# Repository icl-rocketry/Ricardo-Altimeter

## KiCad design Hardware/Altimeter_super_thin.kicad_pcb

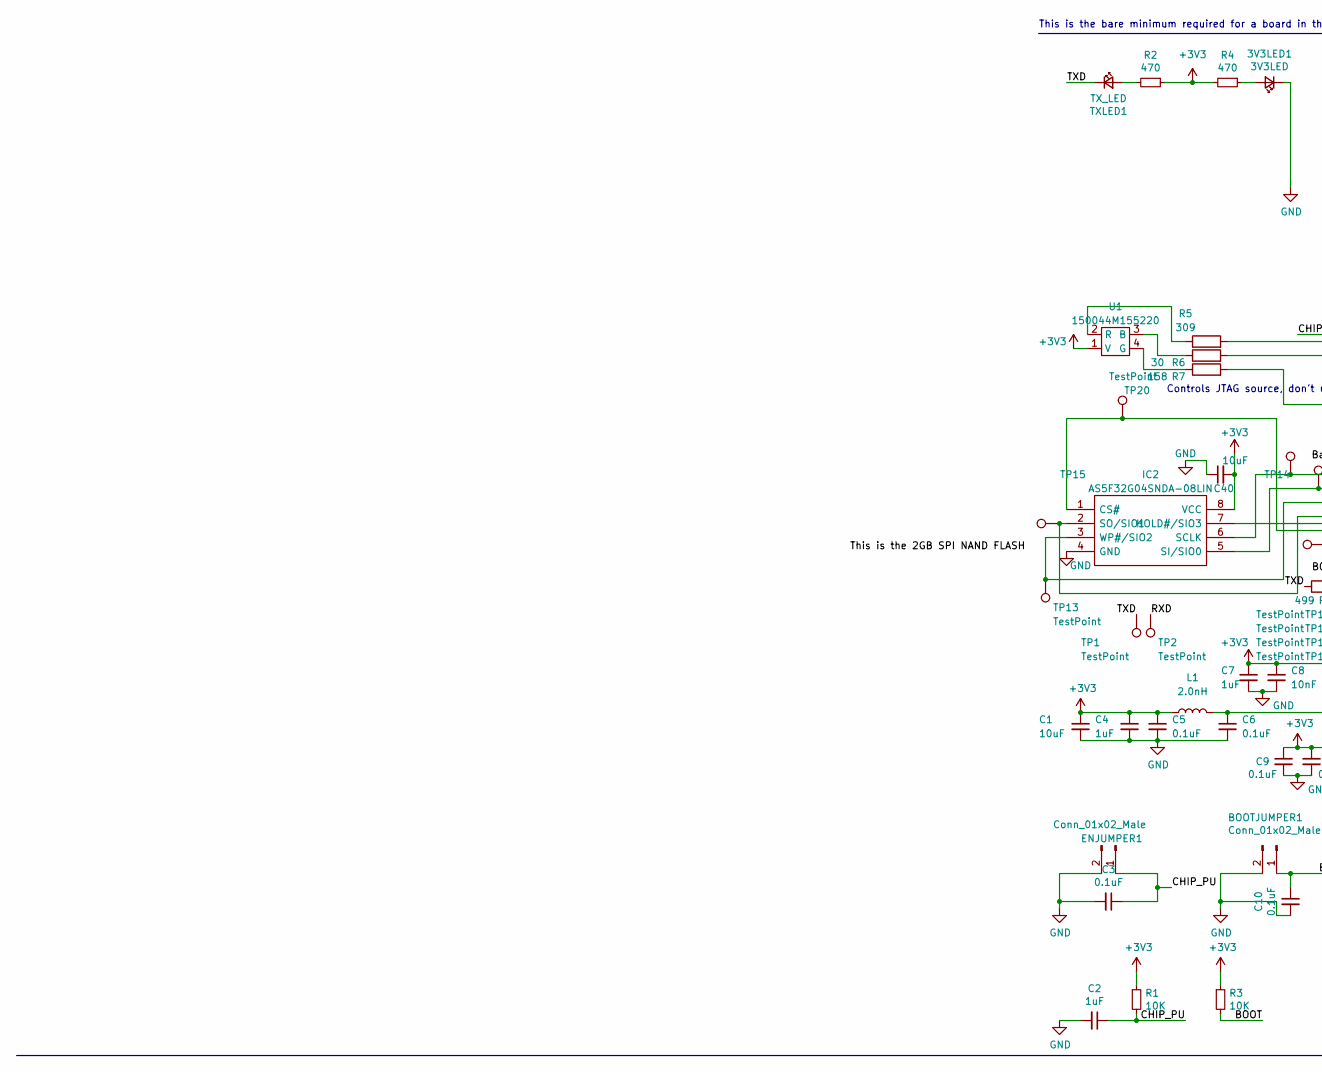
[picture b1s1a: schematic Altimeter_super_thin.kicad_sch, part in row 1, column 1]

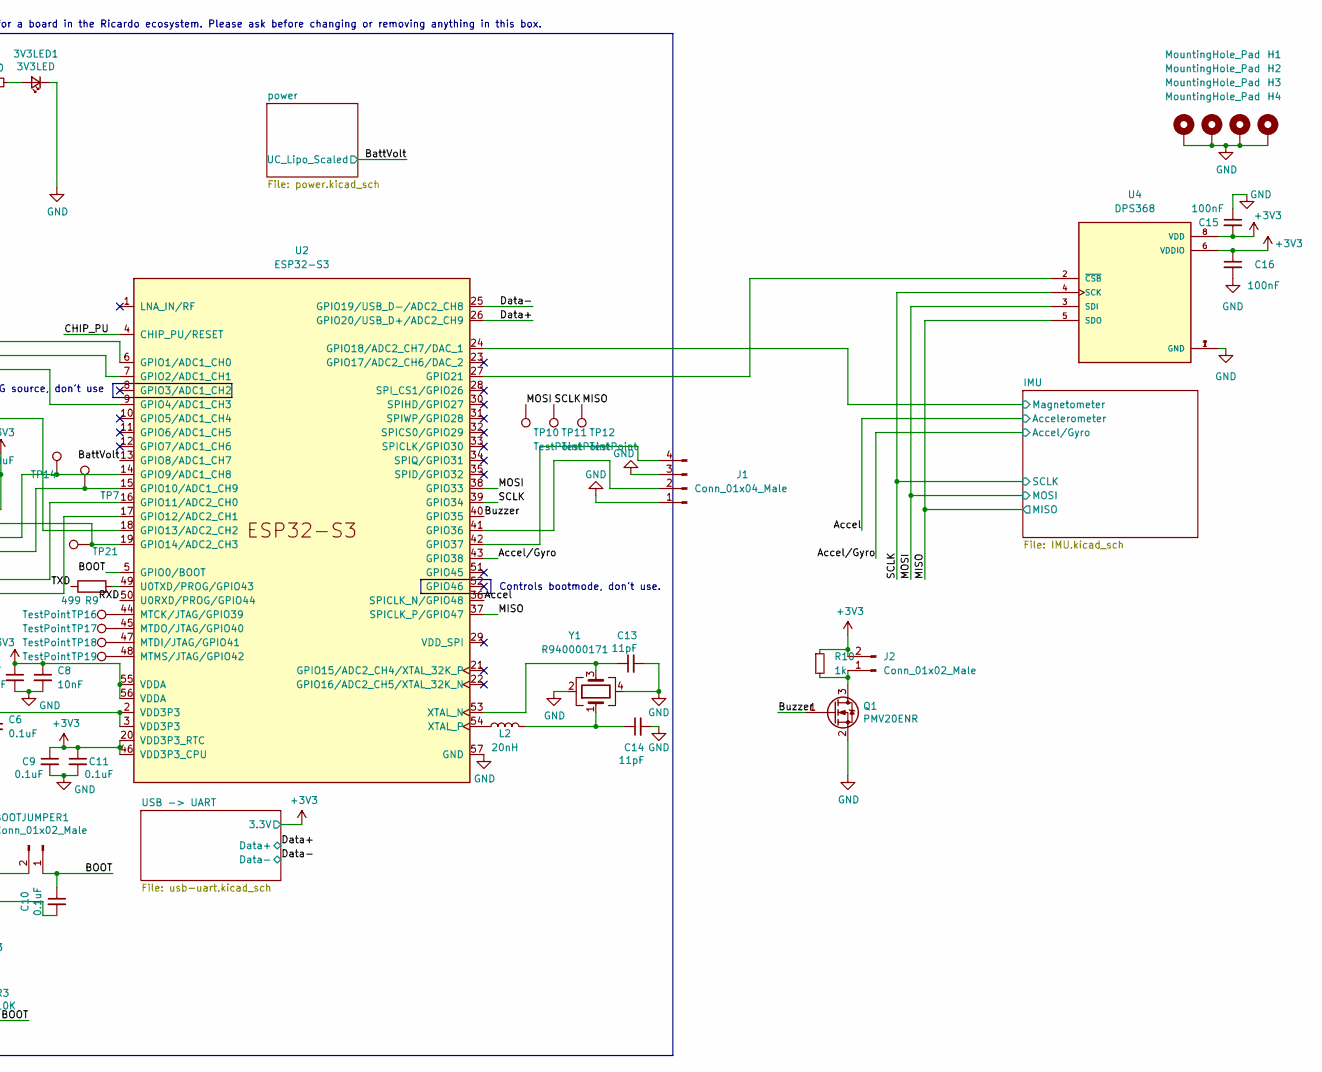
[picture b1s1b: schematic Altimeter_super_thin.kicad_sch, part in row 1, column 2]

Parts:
3V3LED1: 3V3LED; R_0402_1005Metric
BOOTJUMPER1: Conn_01x02_Male; PinHeader_1x02_P2.54mm_Vertical
C1, C40: 10uF; C_0402_1005Metric
C2, C4, C7: 1uF; C_0402_1005Metric
C3, C5, C6, C9, C10, C11: 0.1uF; C_0402_1005Metric
C8: 10nF; C_0402_1005Metric
C13, C14: 11pF; C_0402_1005Metric
C15, C16: 100nF; C_0402_1005Metric
ENJUMPER1: Conn_01x02_Male; PinHeader_1x02_P2.54mm_Vertical
H1, H2, H3, H4: MountingHole_Pad; MountingHole_3.2mm_M3_DIN965
IC2: AS5F32G04SNDA-08LIN; SON127P600X800X65-8N; Manufacturer_Part_Number XTSD08GLGEAG
J1: Conn_01x04_Male; PinHeader_1x04_P2.54mm_Vertical
J2: Conn_01x02_Male; JST_PH_B2B-PH-K_1x02_P2.00mm_Vertical
L1: 2.0nH; L_0402_1005Metric
L2: 20nH; L_0402_1005Metric
Q1: PMV20ENR; SOT-23
R1, R3: 10K; R_0402_1005Metric
R2, R4: 470; R_0402_1005Metric
R5: 309; R_0402_1005Metric
R6: 30; R_0402_1005Metric
R7: 158; R_0402_1005Metric
R9: 499; R_0402_1005Metric
R10: 1k; R_0402_1005Metric
TP1, TP2, TP7, TP10, TP11, TP12, TP13, TP14, TP15, TP16, TP17, TP18, TP19, TP20, TP21: TestPoint; TestPoint_Pad_D1.0mm
TXLED1: TX_LED; R_0402_1005Metric
U1: 150044M155220
U2: ESP32-S3; QFN40P700X700X90-57N
U4: DPS368; XDCR_DPS310
Y1: R940000171; Crystal_SMD_2016-4Pin_2.0x1.6mm

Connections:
+3V3: C1.1, C4.1, C5.1, C7.1, C8.1, C9.1, C11.1, C15.2, C16.1, C40.2, IC2.8 (VCC), J2.2, L1.1, R1.1, R2.1, R3.1, R4.2, R10.1, U1.1 (V), U2.20 (VDD3P3_RTC), U2.46 (VDD3P3_CPU), U2.55 (VDDA), U2.56 (VDDA), U4.6 (VDDIO), U4.8 (VDD); also elsewhere on the board
/Accel: U2.36 (SPICLK_N/GPIO48); also elsewhere on the board
/Accel/Gyro: U2.43 (GPIO38); also elsewhere on the board
/BOOT: BOOTJUMPER1.1, C10.1, R3.2, U2.5 (GPIO0/BOOT)
/BattVolt: U2.13 (GPIO8/ADC1_CH7); also elsewhere on the board
/Buzzer: Q1.1 (G), U2.40 (GPIO35)
/CHIP_PU: C2.1, C3.1, ENJUMPER1.1, R1.2, U2.4 (CHIP_PU/RESET)
/Data+: U2.26 (GPIO20/USB_D+/ADC2_CH9); also elsewhere on the board
/Data-: U2.25 (GPIO19/USB_D-/ADC2_CH8); also elsewhere on the board
/IMU/Magnetometer: U2.24 (GPIO18/ADC2_CH7/DAC_1); also elsewhere on the board
/MISO: TP12.1, U2.37 (SPICLK_P/GPIO47), U4.5 (SDO); also elsewhere on the board
/MOSI: TP10.1, U2.38 (GPIO33), U4.3 (SDI); also elsewhere on the board
/RXD: TP2.1, U2.50 (U0RXD/PROG/GPIO44)
/SCLK: TP11.1, U2.39 (GPIO34), U4.4 (SCK); also elsewhere on the board
/TXD: R9.1, TP1.1, TXLED1.1 (K)
GND: 3V3LED1.1 (K), BOOTJUMPER1.2, C1.2, C2.2, C3.2, C4.2, C5.2, C6.2, C7.2, C8.2, C9.2, C10.2, C11.2, C13.2, C14.2, C15.1, C16.2, C40.1, ENJUMPER1.2, H1.1, H2.1, H3.1, H4.1, IC2.4 (GND), J1.1, J1.3, Q1.2 (S), U2.57 (GND), U4.1 (GND), U4.7 (GND), Y1.2, Y1.4; also elsewhere on the board
unnamed: 3V3LED1.2 (A), R4.1
unnamed: C6.1, L1.2, U2.2 (VDD3P3), U2.3 (VDD3P3)
unnamed: C14.1, L2.2, Y1.1
unnamed: IC2.1 (CS#), TP20.1, U2.18 (GPIO13/ADC2_CH2)
unnamed: IC2.7 (HOLD#/SIO3), TP21.1, U2.19 (GPIO14/ADC2_CH3)
unnamed: IC2.6 (SCLK), TP14.1, U2.14 (GPIO9/ADC1_CH8)
unnamed: IC2.5 (SI/SIO0), TP7.1, U2.15 (GPIO10/ADC1_CH9)
unnamed: IC2.2 (SO/SIO1), TP15.1, U2.17 (GPIO12/ADC2_CH1)
unnamed: IC2.3 (WP#/SIO2), TP13.1, U2.16 (GPIO11/ADC2_CH0)
unnamed: J1.2, U2.41 (GPIO36)
unnamed: J1.4, U2.42 (GPIO37)
unnamed: J2.1, Q1.3 (D), R10.2
unnamed: R2.2, TXLED1.2 (A)
unnamed: R6.1, U1.3 (B)
unnamed: R7.1, U1.4 (G)
unnamed: R5.1, U1.2 (R)
unnamed: R5.2, U2.6 (GPIO1/ADC1_CH0)
unnamed: R6.2, U2.7 (GPIO2/ADC1_CH1)
unnamed: R7.2, U2.9 (GPIO4/ADC1_CH3)
unnamed: U2.27 (GPIO21), U4.2 (~CSB)
unnamed: TP16.1, U2.44 (MTCK/JTAG/GPIO39)
unnamed: TP18.1, U2.47 (MTDI/JTAG/GPIO41)
unnamed: TP17.1, U2.45 (MTDO/JTAG/GPIO40)
unnamed: TP19.1, U2.48 (MTMS/JTAG/GPIO42)
unnamed: R9.2, U2.49 (U0TXD/PROG/GPIO43)
unnamed: C13.1, U2.53 (XTAL_N), Y1.3
unnamed: L2.1, U2.54 (XTAL_P)

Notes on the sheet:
Controls bootmode, don't use.
This is the bare minimum required for a board in the Ricardo ecosystem. Please ask before changing or removing anything in this box.
Controls JTAG source, don't use

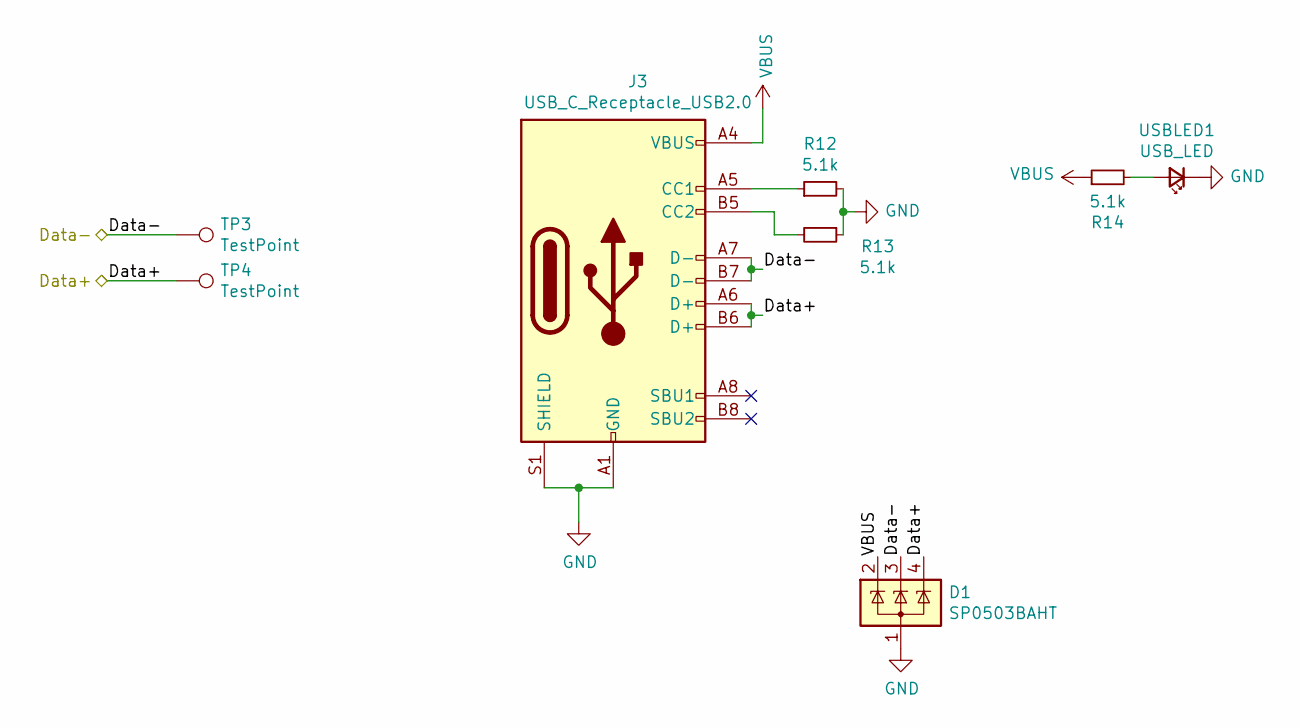
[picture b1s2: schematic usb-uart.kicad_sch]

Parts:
D1: SP0503BAHT; SOT-143
J3: USB_C_Receptacle_USB2.0; USB_C_Receptacle_Palconn_UTC16-G
R12, R13, R14: 5.1k; R_0402_1005Metric
TP3, TP4: TestPoint; TestPoint_Pad_D1.0mm
USBLED1: USB_LED; LED_0402_1005Metric

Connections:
/Data+: D1.4 (K), J3.A6 (D+), J3.B6 (D+), TP4.1; also elsewhere on the board
/Data-: D1.3 (K), J3.A7 (D-), J3.B7 (D-), TP3.1; also elsewhere on the board
GND: D1.1 (A), J3.A1 (GND), J3.A12 (GND), J3.B1 (GND), J3.B12 (GND), J3.S1 (SHIELD), R12.2, R13.1, USBLED1.1 (K); also elsewhere on the board
unnamed: J3.A5 (CC1), R12.1
unnamed: J3.B5 (CC2), R13.2
unnamed: R14.2, USBLED1.2 (A)
VBUS: D1.2 (K), J3.A4 (VBUS), J3.A9 (VBUS), J3.B4 (VBUS), J3.B9 (VBUS), R14.1; also elsewhere on the board

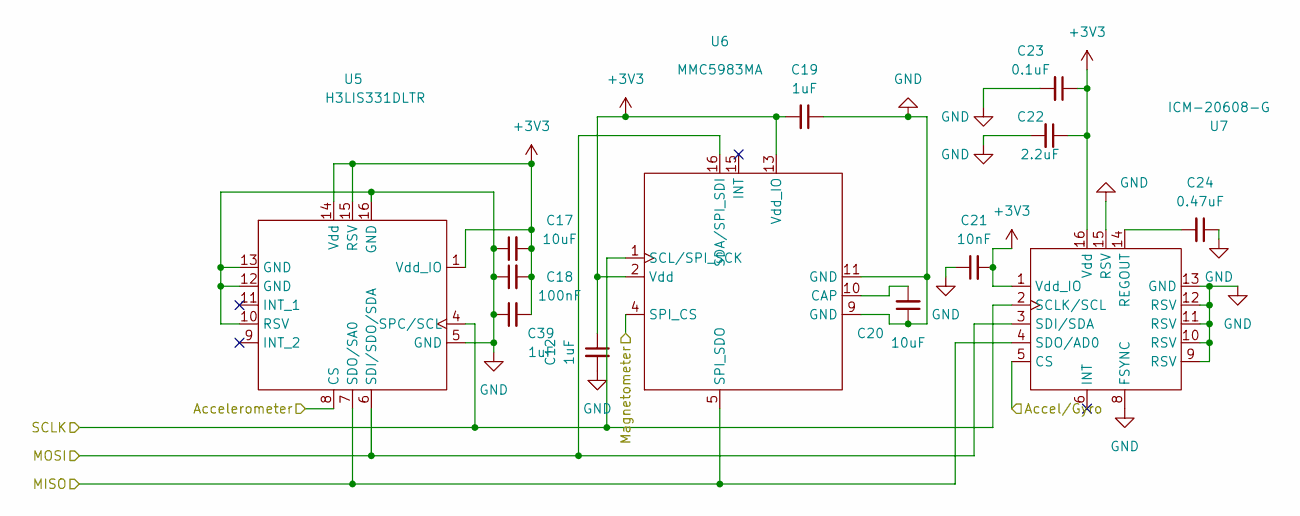
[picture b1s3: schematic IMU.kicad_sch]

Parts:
C12, C19, C39: 1uF; C_0402_1005Metric
C17, C20: 10uF; C_0402_1005Metric
C18: 100nF; C_0402_1005Metric
C21: 10nF; C_0402_1005Metric
C22: 2.2uF; C_0402_1005Metric
C23: 0.1uF; C_0402_1005Metric
C24: 0.47uF; C_0402_1005Metric
U5: H3LIS331DLTR; QFN300X300X100-16N
U6: MMC5983MA; PQFN50P300X300X100-16N
U7: ICM-20608-G; PQFN50P300X300X80-16N

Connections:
+3V3: C12.1, C17.2, C18.2, C19.2, C21.2, C22.1, C23.1, C39.2, U5.1 (Vdd_IO), U5.14 (Vdd), U5.15 (RSV), U6.2 (Vdd), U6.13 (Vdd_IO), U7.1 (Vdd_IO), U7.16 (Vdd); also elsewhere on the board
/Accel: U5.8 (CS); also elsewhere on the board
/Accel/Gyro: U7.5 (CS); also elsewhere on the board
/IMU/Magnetometer: U6.4 (SPI_CS); also elsewhere on the board
/MISO: U5.7 (SDO/SA0), U6.5 (SPI_SDO), U7.4 (SDO/AD0); also elsewhere on the board
/MOSI: U5.6 (SDI/SDO/SDA), U6.16 (SDA/SPI_SDI), U7.3 (SDI/SDA); also elsewhere on the board
/SCLK: U5.4 (SPC/SCL), U6.1 (SCL/SPI_SCK), U7.2 (SCLK/SCL); also elsewhere on the board
GND: C12.2, C17.1, C18.1, C19.1, C20.1, C21.1, C22.2, C23.2, C24.1, C39.1, U5.5 (GND), U5.10 (RSV), U5.12 (GND), U5.13 (GND), U5.16 (GND), U6.9 (GND), U6.11 (GND), U7.8 (FSYNC), U7.9 (RSV), U7.10 (RSV), U7.11 (RSV), U7.12 (RSV), U7.13 (GND), U7.15 (RSV); also elsewhere on the board
unnamed: C20.2, U6.10 (CAP)
unnamed: C24.2, U7.14 (REGOUT)

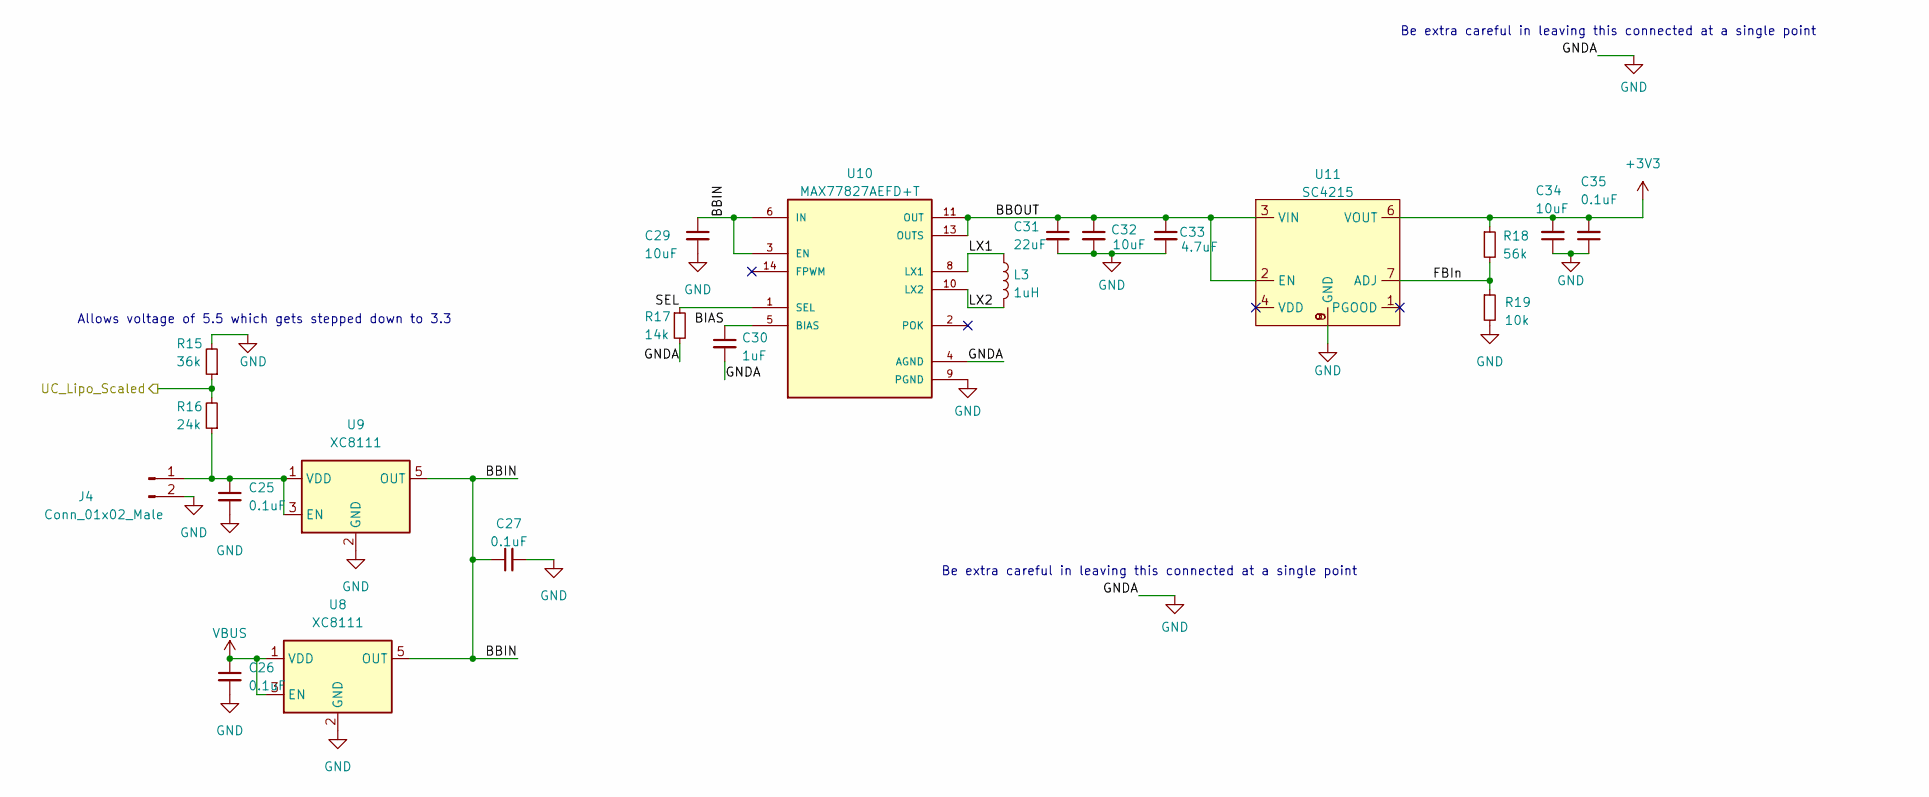
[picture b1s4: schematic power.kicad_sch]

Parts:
C25, C26, C27, C35: 0.1uF; C_0402_1005Metric
C29: 10uF; C_0603_1608Metric
C30: 1uF; C_0402_1005Metric
C31: 22uF; C_0603_1608Metric
C32, C34: 10uF; C_0402_1005Metric
C33: 4.7uF; C_0402_1005Metric
J4: Conn_01x02_Male; JST_PH_B2B-PH-K_1x02_P2.00mm_Vertical
L3: 1uH; L_0805_2012Metric
R15: 36k; R_0402_1005Metric
R16: 24k; R_0402_1005Metric
R17: 14k; R_0402_1005Metric
R18: 56k; R_0402_1005Metric
R19: 10k; R_0402_1005Metric
U8, U9: XC8111; SOT-23-5
U10: MAX77827AEFD+T; CONV_MAX77827AEFD+T; PARTREV B
U11: SC4215; SOIC127P599X175-9N

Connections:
+3V3: C34.2, C35.2, R18.1, U11.6 (VOUT); also elsewhere on the board
/BattVolt: R15.1, R16.2; also elsewhere on the board
/power/BBIN: C27.1, C29.1, U8.5 (OUT), U9.5 (OUT), U10.3 (EN), U10.6 (IN)
/power/BBOUT: C31.1, C32.1, C33.1, U10.11 (OUT), U10.13 (OUTS), U11.2 (EN), U11.3 (VIN)
/power/BIAS: C30.1, U10.5 (BIAS)
/power/FBIn: R18.2, R19.1, U11.7 (ADJ)
/power/LX1: L3.1, U10.8 (LX1)
/power/LX2: L3.2, U10.10 (LX2)
/power/SEL: R17.1, U10.1 (SEL)
GND: C25.2, C26.2, C27.2, C29.2, C30.2, C31.2, C32.2, C33.2, C34.1, C35.1, J4.2, R15.2, R17.2, R19.2, U8.2 (GND), U9.2 (GND), U10.4 (AGND), U10.9 (PGND), U11.8 (GND), U11.9 (GND); also elsewhere on the board
unnamed: C25.1, J4.1, R16.1, U9.1 (VDD), U9.3 (EN)
VBUS: C26.1, U8.1 (VDD), U8.3 (EN); also elsewhere on the board

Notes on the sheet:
Be extra careful in leaving this connected at a single point
Allows voltage of 5.5 which gets stepped down to 3.3

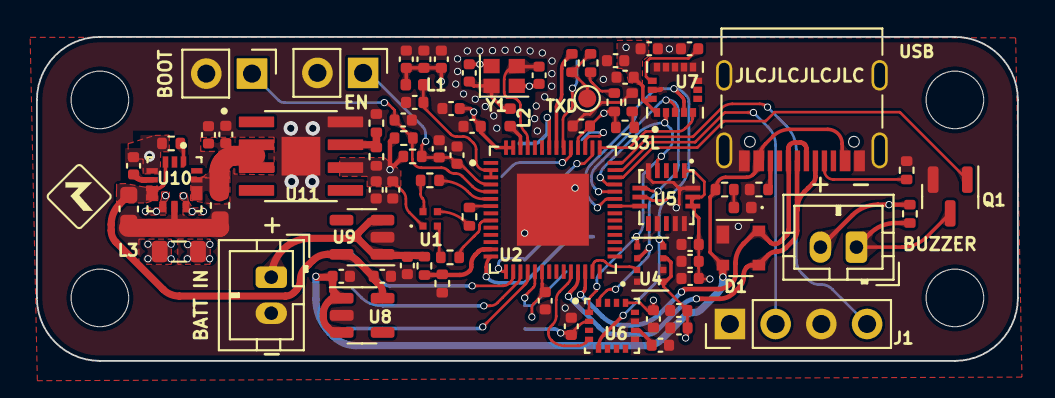
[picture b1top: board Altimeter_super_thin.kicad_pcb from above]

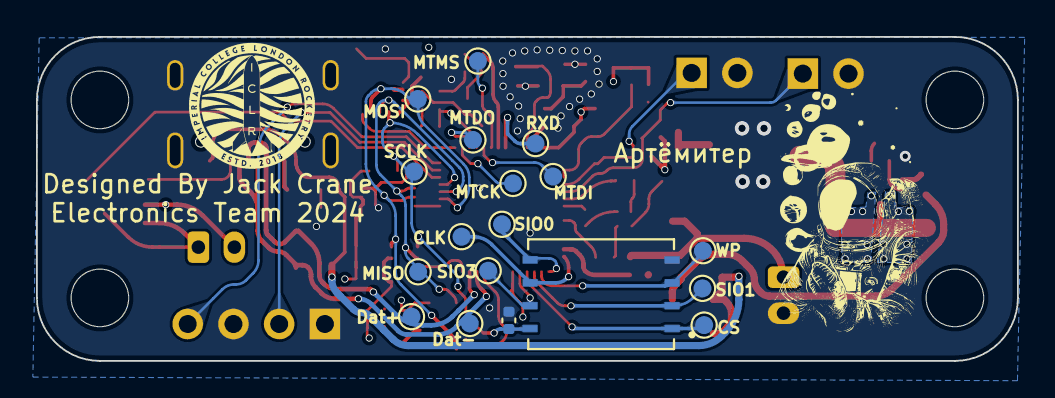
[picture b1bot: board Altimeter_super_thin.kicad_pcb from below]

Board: 4 copper layers, 54.5 x 18.0 mm, 100 parts (18 on the bottom side), 57 nets.

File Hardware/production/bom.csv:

Designator,Footprint,Quantity,Value,LCSC Part #
3V3LED1,0402,1,3V3LED,
"BOOTJUMPER1, ENJUMPER1",PinHeader_1x02_P2.54mm_Vertical,2,Conn_01x02_Male,
"C1, C17, C20, C32, C34, C40",0402,6,10uF,
"C10, C11, C23, C25, C26, C27, C3, C35, C5, C6, C9",0402,11,0.1uF,
"C12, C19, C2, C30, C39, C4, C7",0402,7,1uF,
"C13, C14",0402,2,C,
"C15, C16, C18",0402,3,100nF,
"C21, C8",0402,2,10nF,
C22,0402,1,2.2uF,
C24,0402,1,0.47uF,
C29,0603,1,10uF,
C31,0603,1,22uF,
C33,0402,1,4.7uF,
D1,SOT-143,1,SP0503BAHT,
"H1, H2, H3, H4",MountingHole_3.2mm_M3_DIN965,4,MountingHole_Pad,
IC2,SON127P600X800X65-8N,1,AS5F32G04SNDA-08LIN,
J1,PinHeader_1x04_P2.54mm_Vertical,1,Conn_01x04_Male,
"J2, J4",JST_PH_B2B-PH-K_1x02_P2.00mm_Vertical,2,Conn_01x02_Male,
J3,USB_C_Receptacle_Palconn_UTC16-G,1,USB_C_Receptacle_USB2.0,
L1,0402,1,2.0nH,
L2,0402,1,20nH,
L3,0805,1,1uH,
Q1,SOT-23,1,PMV20ENR,
"R1, R19, R3",0402,3,10K,
R10,0402,1,1k,
"R12, R13, R14",0402,3,5.1k,
R15,0402,1,36k,
R16,0402,1,24k,
R17,0402,1,14k,
R18,0402,1,56k,
"R2, R4",0402,2,470,
R5,0402,1,309,
R6,0402,1,30,
R7,0402,1,158,
R9,0402,1,499,
"TP1, TP10, TP11, TP12, TP13, TP14, TP15, TP16, TP17, TP18, TP19, TP2, TP20, TP21, TP3, TP4, TP7",TestPoint_Pad_D1.0mm,17,TestPoint,
TXLED1,0402,1,TX_LED,
U1,150044M155220,1,150044M155220,
U10,CONV_MAX77827AEFD+T,1,MAX77827AEFD+T,
U11,SOIC127P599X175-9N,1,SC4215,
U2,QFN40P700X700X90-57N,1,ESP32-S3,
U4,XDCR_DPS310,1,DPS368,
U5,QFN300X300X100-16N,1,H3LIS331DLTR,
U6,PQFN50P300X300X100-16N,1,MMC5983MA,
U7,PQFN50P300X300X80-16N,1,ICM-20608-G,
"U8, U9",SOT-23-5,2,XC8111,
USBLED1,0402,1,USB_LED,
Y1,Crystal_SMD_2016-4Pin_2.0x1.6mm,1,40MHz±10ppm,

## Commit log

2023-01-28 added power sensors and working on led
2023-01-28 added led
2023-01-31 final commit pre-review
2023-02-28 Pre-Initial review
2023-05-09 2nd iteration to be reviewed
2023-05-17 3rd iteration
2023-05-19 3rd iteration with new tracer spacing of 0.15
2023-05-20 hopefully final commit
2023-06-11 started making it thinner but realised it could be even thinner
2023-07-01 spaced out vias and changed j4
2023-12-09 initial stage of reitteration
2024-03-16 rerouted spi bus and changed NAND
2024-04-19 fixed courtyard overlap in one place
2024-05-19 Ordering changes
2024-05-19 Post merge cleanup
2024-05-19 Regenerated production files to add RAE logo
2024-06-25 reformatting files
2024-10-13 code on altimeter during flight
2025-09-13 pretty sure the ftl is working now
2025-09-15 Add submodules (create gitlinks)
2025-09-15 Add submodules (create gitlinks) under Firmware/components
2025-09-15 Move submodules under Firmware/{components,external}
2025-09-17 updated to esp idf 5.3
2025-09-18 new branch to get msc working
2025-09-28 getting closer, msc could work with this sdkconfig but packet sending is broken
2025-09-28 removed the two libs i dont think i need
2025-10-05 esp logs work but packets dont, pushing beofre i mess it up trying to get msc to work
2025-10-06 msc works on this if youre not looking at serial when trying to get data back
2025-10-06 base implementation working, want to fix rnp packet problem
2025-10-11 currently fully working, need to speed up. still no ricardo functionality
2025-10-13 final flight code
2025-10-27 updating available states
2025-11-28 might be in too deep with getting the msc + ricardo to work
